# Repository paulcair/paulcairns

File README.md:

# Paul Cairns - Portfolio Page

This is the repository that contains all of the information about Paul Cairns. It is a portfolio of his work.

## Usage

Clone the repository to get access to my project files and edit it according to your needs.

## Webpage

You can navigate through to see his projects and porfolio,as well as an overview of his career and blog posts following URL: www.paul-cairns.com Enjoy the page! Should you have any questions. Leave a comment, or email me at paulcair@gmail.com

Enjoy!

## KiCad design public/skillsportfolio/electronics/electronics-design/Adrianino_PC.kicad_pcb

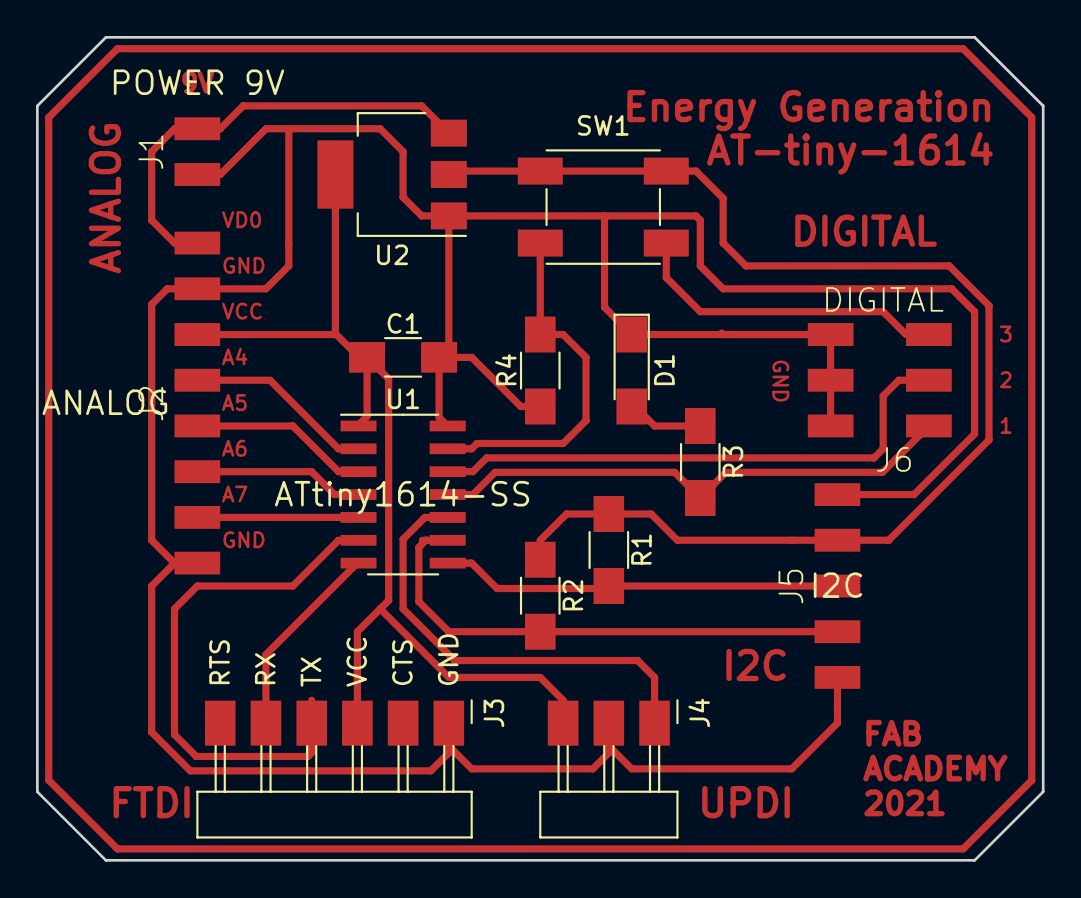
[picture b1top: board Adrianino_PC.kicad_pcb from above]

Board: 2 copper layers, 55.9 x 45.7 mm, 15 parts (0 on the bottom side), 16 nets.

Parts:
C1: 1uF; C_1206
D1: LED; LED_1206
J1: POWER 9V; fab-1X02SMD
J2: ANALOG; fab-1X08SMD
J3: FTDI; Header_SMD_FTDI_01x06_P2.54mm_Horizontal_Male
J4: UPDI; Header_SMD_01x03_P2.54mm_Horizontal_Male
J5: I2C; fab-1X05SMD
J6: DIGITAL; fab-2X03SMD
R1, R2: 4.99k; R_1206
R3: 499; R_1206
R4: 1k; R_1206
SW1: BUTTON; Button_Omron_B3SN_6x6mm
U1: ATtiny1614-SS; SOIC-14_3.9x8.7mm_P1.27mm
U2: VREG; SOT-223-3_TabPin2

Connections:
/GND: C1.2, D1.1, J1.2, J2.2, J2.8, J3.1, J4.2, J5.1, J5.5, J6.2, J6.4, J6.6, R4.1, U1.14, U2.1
/PA1: J6.1, R3.2, U1.11
/PA2: J6.3, U1.12
/PA3: J6.5, R4.2, SW1.2, U1.13
/PA4: J2.4, U1.2
/PA5: J2.5, U1.3
/PA6: J2.6, U1.4
/PA7: J2.7, U1.5
/RX: J3.5, U1.7
/SCL: J5.4, R2.2, U1.9
/SDA: J5.3, R1.2, U1.8
/TX: J3.4, U1.6
/UPDI: J4.1, U1.10
/VCC: C1.1, J2.3, J3.3, J4.3, J5.2, R1.1, R2.1, SW1.1, U1.1, U2.2
/VD0: J1.1, J2.1, U2.3
unnamed: D1.2, R3.1

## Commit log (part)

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2023-11-22 first version of the site
2023-11-25 Minor change
2023-12-06 Updated the logo
2023-12-08 Changed colors
2023-12-08 Changed colors. Need to upload the headshot photo to obtain the color pallet for the branding
2023-12-08 Colors updated
2023-12-09 updated logo
2024-01-02 Minor changes. Need to sort out the navbar. See the EnergyLab page navbar for guidance.
2024-01-03 Have debugged the navbar colors. Need to get the button toggling and the bar showing the options instead of the toggle button
2024-01-06 Got the navbar colors good. Still need to debug the collapse funcitonality as well as why it isn't showing properly when the size changes
2024-01-07 Adding backup BeltyV2 CAD files
2024-01-07 Uploading latest CAD files
2024-01-08 Updated the BeltyV2 page to include the modelling and FEA work that was performed
2024-01-08 Formated the cards so the background is white
2024-01-09 Have updated the formatting to work well for everything I have seen so far. Time to start populating the site. Also, I need to fix the formatting for the about card
2024-01-10 did an oopsie
2024-01-10 Revert "Have updated the formatting to work well for everything I have seen so far. Time to start populating the site. Also, I need to fix the formatting for the about card"
    This reverts commit ca929369e94cae7946c78fd1ee936bc8978f76cf.
2024-01-10 Changed the assignments to skills portfolio
2024-01-11 Added MIT App inventor skill to portfolio
2024-01-12 Have added the CAD week and tailored it more to my portfolio page. Next need to update the layout of the skills pages to be a bunch of cards that show each sub-skill. For example the CAD page will ha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
2024-01-15 Have added the skills sections. Need to get the skill index page rendering correctly so that it shows the subpages
2024-01-16 Have got the section layout template working. Need to go and fix the _index.md header sections for each skill using the CAD version as a template. Then finally I can start populating the site. May ne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
2024-01-17 Have finalized the template of the website with all the sections. Time to start adding content
2024-01-19 Have started adding some of the Fab Academy assignments
2024-01-19 Added a link to my github account on my programming page
2024-01-22 Have added a bunch more fab academy assignments. Need to add them all
2024-01-23 Added more Fab Academy Assignments
2024-01-23 Added the final Fab Academy Assignment
2024-01-23 All Fab Academy Assignments are uploaded. Next, need to add extra laser cutting skills you have done, or change them all to _index.md. Can also add aluminum casting to skillset for molding and castin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
2024-01-23 Updated the about card to be the full width of the page
2024-01-25 Adding the video templates
2024-01-25 Video template complete, need to add them to the website now
2024-01-29 small change
2024-01-30 Adding more videos
2024-01-30 Added more video appearances
2024-01-31 Added the turnbull video. Next need to start adding publications and the like.
2024-02-06 Added some of my publications
2024-02-21 Changes to formatting of pages
2024-02-22 Minor change to h1
2024-02-22 Changing headings
2024-02-22 Cleaned up sheet metal forming week
2024-02-27 Added the ENERGICA report
2024-03-01 Figuring out embedded YouTube videos
2024-03-01 Fixed the youtube problem by updating to https rather than http
2024-03-02 Adding the OnShape modeling page
2024-03-03 adding the SLA printer workflow
2024-03-03 have added all of the SLA slicing workflow
2024-03-03 added some changes to SLA workflow
2024-03-10 Adding Solidworks stuff
2024-03-12 Added the SLA printing photos and videos. Need to add the documentation and reference the images
2024-03-13 adding images to Solidworks page
2024-03-13 added SLA printer images to page
2024-03-13 added blog post
2024-03-13 added image to blog post
2024-03-13 removed technical jargon blog post
2024-03-14 added hiprox paper
2024-03-14 added citation to hiprox paper
2024-03-15 added the art of mopping
2024-03-16 added some photos of the face follower assembly to the Solidworks page
2024-03-18 Added face-follower project
2024-03-18 Added face-follower project 3D printed photos
2024-03-19 Added the ted talk as a blog post
2024-03-19 Added the paver publication
2024-03-27 Added degrees
2024-03-28 started the 6 DOF robot arm project
2024-03-28 added dh coordinates discussion
2024-03-28 geppeto
2024-03-28 geppeto minor changes
2024-03-31 added some dh coord discussion
2024-04-01 spiral Tree
2024-04-02 added anycubic photo
2024-04-02 ensuring the tree vid is there
2024-04-02 minor adjustment
2024-04-03 Adding DCSG
2024-04-04 Added photo of me at energylab
2024-04-04 dcsg video
2024-04-04 dcsg video and other minor adjustments
2024-08-16 Added my TEDx Talk
2024-10-28 Updating 6DOF page
2024-11-30 updating forwardKinematics.py -> Have added a way to input desired angles, convert those into servo values, and send the command to move the Robot through the moveRobot script. Also have defined the 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
2024-12-02 Updating the 6DOF robot page
2024-12-10 updating forwardKinematics.py -> Have added a way to input desired angles, convert those into servo values, and send the command to move the Robot through the moveRobot script. Also have defined the 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
